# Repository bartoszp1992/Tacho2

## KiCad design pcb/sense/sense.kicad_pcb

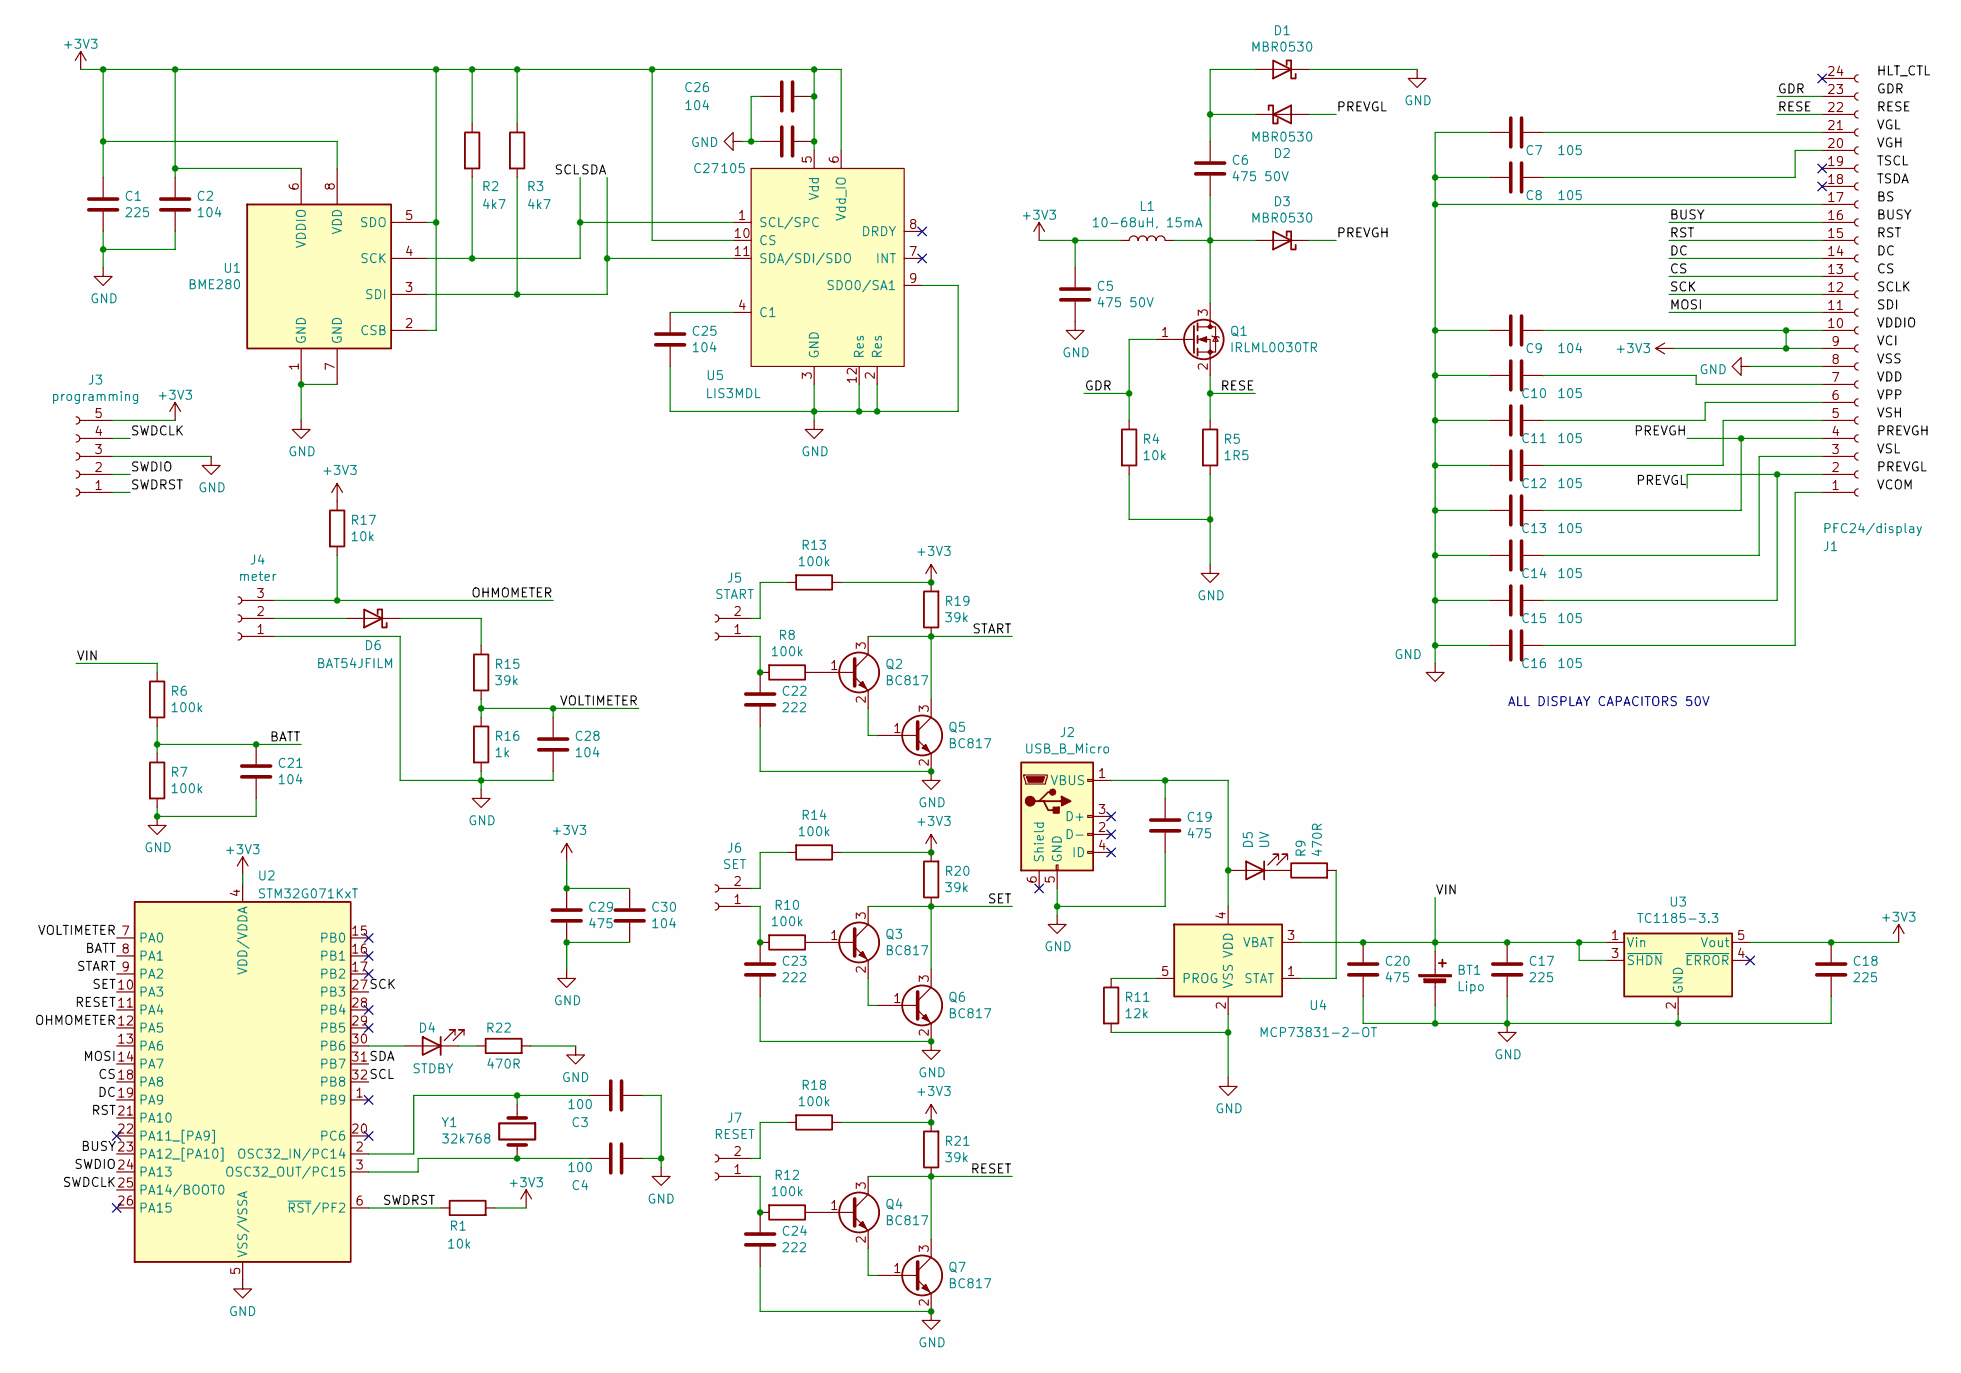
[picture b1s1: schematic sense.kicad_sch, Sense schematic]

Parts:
BT1: Lipo; R_2010_5025Metric
C1, C17, C18: 225; C_0603_1608Metric
C2, C9, C21, C25, C26, C28, C30: 104; C_0603_1608Metric
C3, C4: 100; C_0603_1608Metric
C5, C6: 475 50V; C_0805_2012Metric
C7, C8, C10, C11, C12, C13, C14, C15, C16, C27: 105; C_0603_1608Metric
C19, C20, C29: 475; C_0603_1608Metric
C22, C23, C24: 222; C_0603_1608Metric
D1, D2, D3: MBR0530; D_SOD-123
D4: STDBY; LED_0603_1608Metric
D5: UV; D_0603_1608Metric
D6: BAT54JFILM; D_SOD-323
J1: PFC24/display; FPC-24P-P0.50mm_Universal
J2: USB_B_Micro; USB_Micro-B_Molex_47346-0001
J3: programming; PinHeader_1x05_P1.27mm_Vertical
J4: meter; PinHeader_1x03_P1.27mm_Horizontal
J5: START; PinHeader_1x02_P2.54mm_Vertical
J6: SET; PinHeader_1x02_P2.54mm_Vertical
J7: RESET; PinHeader_1x02_P2.54mm_Vertical
L1: 10-68uH, 15mA; R_1206_3216Metric
Q1: IRLML0030TR; SOT-23
Q2, Q3, Q4, Q5, Q6, Q7: BC817; SOT-23
R1, R4, R17: 10k; R_0603_1608Metric
R2, R3: 4k7; R_0603_1608Metric
R5: 1R5; R_0603_1608Metric
R6, R7, R8, R10, R12, R13, R14, R18: 100k; R_0603_1608Metric
R9, R22: 470R; R_0603_1608Metric
R11: 12k; R_0603_1608Metric
R15, R19, R20, R21: 39k; R_0603_1608Metric
R16: 1k; R_0603_1608Metric
U1: BME280; Bosch_LGA-8_2.5x2.5mm_P0.65mm_ClockwisePinNumbering
U2: STM32G071KxT; LQFP-32_7x7mm_P0.8mm
U3: TC1185-3.3; SOT-23-5
U4: MCP73831-2-OT; SOT-23-5
U5: LIS3MDL; LGA-12_2x2mm_P0.5mm
Y1: 32k768; Crystal_DS26_D2.0mm_L6.0mm_Horizontal

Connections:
+3V3: C1.1, C2.1, C5.1, C9.1, C18.1, C26.1, C27.1, C29.1, C30.1, J1.9, J1.10, J3.5, L1.1, R1.2, R2.1, R3.1, R13.1, R14.1, R17.1, R18.1, R19.2, R20.2, R21.2, U1.2 (CSB), U1.5 (SDO), U1.6 (VDDIO), U1.8 (VDD), U2.4 (VDD/VDDA), U3.5 (Vout), U5.5 (Vdd), U5.6 (Vdd_IO), U5.10 (CS)
/BATT: C21.1, R6.2, R7.1, U2.8 (PA1)
/BUSY: J1.16, U2.23 (PA12_[PA10])
/CS: J1.13, U2.18 (PA8)
/DC: J1.14, U2.19 (PA9)
/GDR: J1.23, Q1.1 (G), R4.1
/MOSI: J1.11, U2.14 (PA7)
/OHMOMETER: J4.3, R17.2, U2.12 (PA5)
/PREVGH: C13.1, D3.1 (K), J1.4
/PREVGL: C15.1, D2.2 (A), J1.2
/RESE: J1.22, Q1.2 (S), R5.1
/RESET: Q4.3 (C), Q7.3 (C), R21.1, U2.11 (PA4)
/RST: J1.15, U2.21 (PA10)
/SCK: J1.12, U2.27 (PB3)
/SCL: R2.2, U1.4 (SCK), U2.32 (PB8), U5.1 (SCL/SPC)
/SDA: R3.2, U1.3 (SDI), U2.31 (PB7), U5.11 (SDA/SDI/SDO)
/SET: Q3.3 (C), Q6.3 (C), R20.1, U2.10 (PA3)
/START: Q2.3 (C), Q5.3 (C), R19.1, U2.9 (PA2)
/SWDCLK: J3.4, U2.25 (PA14/BOOT0)
/SWDIO: J3.2, U2.24 (PA13)
/SWDRST: J3.1, R1.1, U2.6 (~RST/PF2)
/VIN: BT1.1 (+), C17.1, C20.1, R6.1, U3.1 (Vin), U3.3 (~SHDN), U4.3 (VBAT)
/VOLTIMETER: C28.1, R15.2, R16.1, U2.7 (PA0)
GND: BT1.2 (-), C1.2, C2.2, C3.2, C4.2, C5.2, C7.2, C8.2, C9.2, C10.2, C11.2, C12.2, C13.2, C14.2, C15.2, C16.2, C17.2, C18.2, C19.2, C20.2, C21.2, C22.2, C23.2, C24.2, C25.2, C26.2, C27.2, C28.2, C29.2, C30.2, D1.1 (K), J1.8, J1.17, J2.5 (GND), J3.3, J4.1, Q5.2 (E), Q6.2 (E), Q7.2 (E), R4.2, R5.2, R7.2, R11.2, R16.2, R22.2, U1.1 (GND), U1.7 (GND), U2.5 (VSS/VSSA), U3.2 (GND), U4.2 (VSS), U5.2 (Res), U5.3 (GND), U5.9 (SDO0/SA1), U5.12 (Res)
unnamed: C3.1, U2.2 (OSC32_IN/PC14), Y1.1
unnamed: C4.1, U2.3 (OSC32_OUT/PC15), Y1.2
unnamed: C6.1, D1.2 (A), D2.1 (K)
unnamed: C6.2, D3.2 (A), L1.2, Q1.3 (D)
unnamed: C7.1, J1.21
unnamed: C8.1, J1.20
unnamed: C10.1, J1.7
unnamed: C11.1, J1.6
unnamed: C12.1, J1.5
unnamed: C14.1, J1.3
unnamed: C16.1, J1.1
unnamed: C19.1, D5.2 (A), J2.1 (VBUS), U4.4 (VDD)
unnamed: C22.1, J5.1, R8.2
unnamed: C23.1, J6.1, R10.2
unnamed: C24.1, J7.1, R12.2
unnamed: C25.1, U5.4 (C1)
unnamed: D4.1 (K), R22.1
unnamed: D4.2 (A), U2.30 (PB6)
unnamed: D5.1 (K), R9.1
unnamed: D6.1 (K), R15.1
unnamed: D6.2 (A), J4.2
unnamed: J5.2, R13.2
unnamed: J6.2, R14.2
unnamed: J7.2, R18.2
unnamed: Q2.1 (B), R8.1
unnamed: Q2.2 (E), Q5.1 (B)
unnamed: Q3.1 (B), R10.1
unnamed: Q3.2 (E), Q6.1 (B)
unnamed: Q4.1 (B), R12.1
unnamed: Q4.2 (E), Q7.1 (B)
unnamed: R9.2, U4.1 (STAT)
unnamed: R11.1, U4.5 (PROG)

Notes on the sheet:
ALL DISPLAY CAPACITORS 50V

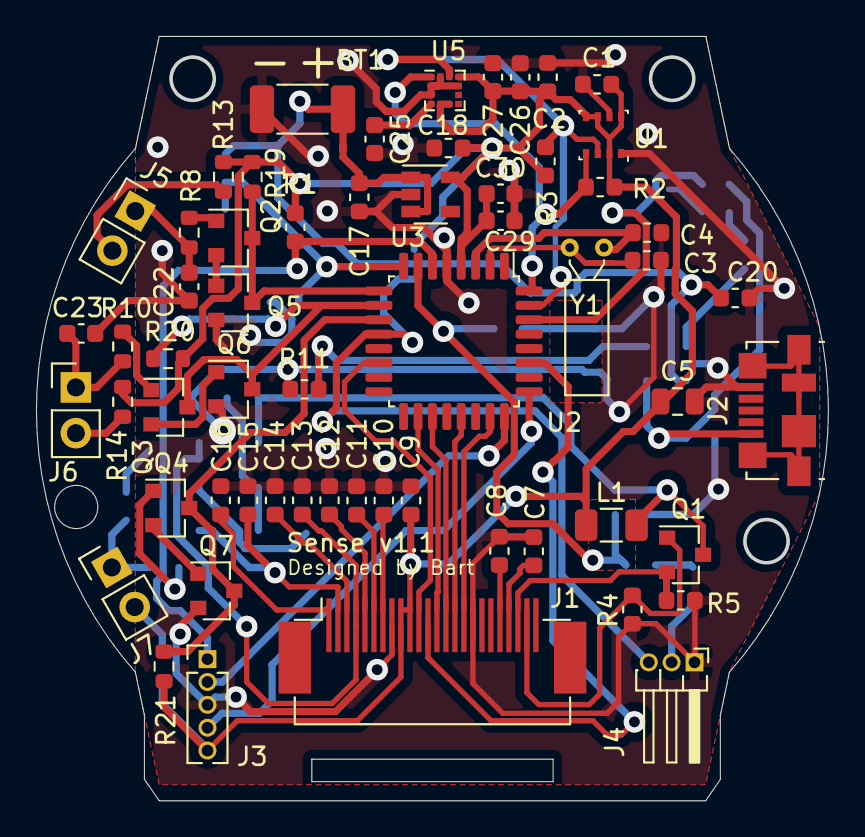
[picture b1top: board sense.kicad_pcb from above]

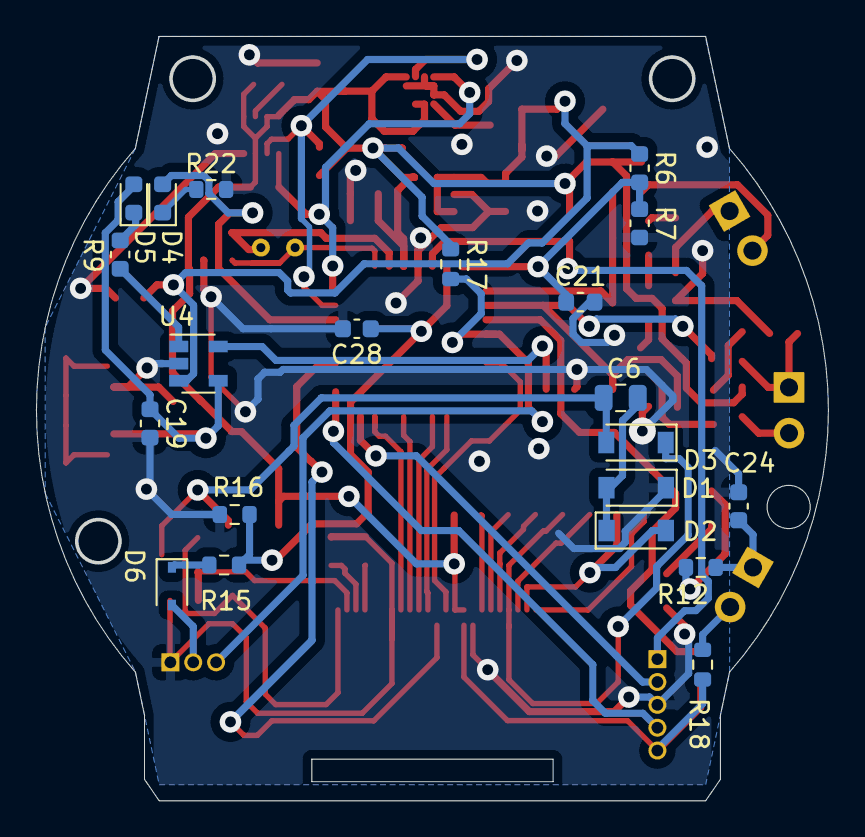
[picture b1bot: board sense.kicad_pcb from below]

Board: 2 copper layers, 44.0 x 42.5 mm, 80 parts (21 on the bottom side), 56 nets.

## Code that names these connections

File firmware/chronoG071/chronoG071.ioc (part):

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Mcu.Name=STM32G071K(6-8-B)Tx
Mcu.Package=LQFP32
Mcu.UserName=STM32G071KBTx
PA0.GPIOParameters=GPIO_Label
PA0.GPIO_Label=PASSIVE
PA0.Mode=IN0
PA0.Signal=ADC1_IN0
PA1.GPIOParameters=GPIO_Label
PA1.GPIO_Label=BATT
PA1.Mode=IN1
PA1.Signal=ADC1_IN1
PA10.GPIOParameters=GPIO_Label
PA10.GPIO_Label=RST
PA10.Signal=GPIO_Output
PA12\ [PA10].GPIOParameters=GPIO_Label
PA12\ [PA10].GPIO_Label=BUSY
PA12\ [PA10].Signal=GPIO_Input
PA13.Mode=Serial_Wire
PA13.Signal=SYS_SWDIO
PA14-BOOT0.Mode=Serial_Wire
PA14-BOOT0.Signal=SYS_SWCLK
PA2.GPIOParameters=GPIO_PuPd,GPIO_Label,GPIO_ModeDefaultEXTI
PA2.GPIO_Label=START
PA2.GPIO_ModeDefaultEXTI=GPIO_MODE_IT_FALLING
PA2.GPIO_PuPd=GPIO_PULLUP
PA2.Signal=GPXTI2
PA3.GPIOParameters=GPIO_PuPd,GPIO_Label,GPIO_ModeDefaultEXTI
PA3.GPIO_Label=SET
PA3.GPIO_ModeDefaultEXTI=GPIO_MODE_IT_FALLING
PA3.GPIO_PuPd=GPIO_PULLUP
PA3.Signal=GPXTI3
PA4.GPIOParameters=GPIO_PuPd,GPIO_Label,GPIO_ModeDefaultEXTI
PA4.GPIO_Label=RESET
PA4.GPIO_ModeDefaultEXTI=GPIO_MODE_IT_FALLING
PA4.GPIO_PuPd=GPIO_PULLUP
PA4.Signal=GPXTI4
PA5.GPIOParameters=GPIO_Label
PA5.GPIO_Label=ACTIVE
PA5.Mode=IN5
PA5.Signal=ADC1_IN5
PA7.GPIOParameters=GPIO_Speed,PinState
PA7.GPIO_Speed=GPIO_SPEED_FREQ_HIGH
PA7.Mode=TX_Only_Simplex_Unidirect_Master
PA7.PinState=GPIO_PIN_RESET
PA7.Signal=SPI1_MOSI
PA8.GPIOParameters=GPIO_Label
PA8.GPIO_Label=SPI_CS
PA8.Signal=GPIO_Output
PA9.GPIOParameters=GPIO_Label
PA9.GPIO_Label=DC
PA9.Signal=GPIO_Output
PB3.GPIOParameters=GPIO_Speed
PB3.GPIO_Speed=GPIO_SPEED_FREQ_HIGH
PB3.Mode=TX_Only_Simplex_Unidirect_Master
PB3.Signal=SPI1_SCK
PB6.GPIOParameters=GPIO_Label
PB6.GPIO_Label=STATUS
PB6.Signal=GPIO_Output
PB7.GPIOParameters=GPIO_Pu
PB7.GPIO_Pu=GPIO_PULLUP
PB7.Mode=I2C
PB7.Signal=I2C1_SDA
PB8.GPIOParameters=GPIO_Pu
PB8.GPIO_Pu=GPIO_PULLUP
PB8.Mode=I2C
PB8.Signal=I2C1_SCL
PC14-OSC32_IN\ (PC14).Mode=LSE-External-Oscillator
PC14-OSC32_IN\ (PC14).Signal=RCC_OSC32_IN
PC15-OSC32_OUT\ (PC15).Mode=LSE-External-Oscillator
PC15-OSC32_OUT\ (PC15).Signal=RCC_OSC32_OUT
RCC.HSE_VALUE=8000000
RCC.SYSCLKFreq_VALUE=64000000
RCC.SYSCLKSource=RCC_SYSCLKSOURCE_PLLCLK
board=custom

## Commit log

2021-08-14 2.7.3
2021-08-24 2.7.4
2021-08-30 increased magnetometer divider
2021-08-30 corrected bug in switching 5->3 layout
2021-09-27 minor
2021-10-02 added moon phase display
2021-10-03 2.8.1
2022-01-04 v3.0
2022-01-04 moved files
2022-01-20 3.11
2022-02-23 properly working on weak battery
2022-03-17 added flash backup, refactored code
2022-03-18 added license
2022-03-18 updated license
2022-03-31 corrected chronograph
2022-04-01 corrected low batteryflag name
2022-06-22 PCB project converted for kicad 6
2022-06-28 updated for G071, PCB sense v1.0
2022-07-04 larger C5
2022-07-13 PCB v1.1
